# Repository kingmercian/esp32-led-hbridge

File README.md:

# ESP32 LED Controller

Schematic and PCB design for an ESP32, specifically a Wemos Lolin D2 mini shield to control low power (~200mA) monochromatic fairy lights. These monochromatic fairy lights function as bidirectional LEDs, where alternating the polarity on the two wires changes which half of the LEDs illuminate.

## Why?

My wife frequently purchases cheap battery/USB monochrome string lights at stores locally or online retailers such as Aliexpress. I wanted to be able to take advantage of these lights to automate them in my home automation system, namely a set we have covering our curtains that I would like to toggle based on sunset. https://www.aliexpress.com/item/1005007634861597.html

I was looking for a device to satisfy the following requirements:
* The device should be able to control at least one set of string lights.
* The device should be able to control the brightness of the lights.
* The device should be able to control them via  [Home Assistant](https://home-assistant.io/).

## Software
ESPHome configuration:
https://github.com/kingmercian/esphome/blob/4c16731de8fa22333e613f6e8b42984a3e44136c/curtain-leds.yaml

## Schematic

## PCB

## Render

## Parts List
| Part | Type | Footprint | Designator  | Quantity
|--|--|--|--|--|
| ESP32 S2 Mini | Microcontroller | N/A | N/A | 1 |
| 1K | Resistor| 0805 | R1, R2, R3, R4 | 4 |
| MMBT2907 | Transistor | SOT-23 | Q1, Q3 | 2 |
| MMBT2222 | Transistor | SOT-23 | Q2, Q4 | 2 |

## Issues
None for my usage but if I build these in future I would make some changes:
* add a diode between the transistor and LED output
* add terminal blocks to attach LEDs
* add button to toggle through LED patterns (control through software)
* add switch to disable LED output

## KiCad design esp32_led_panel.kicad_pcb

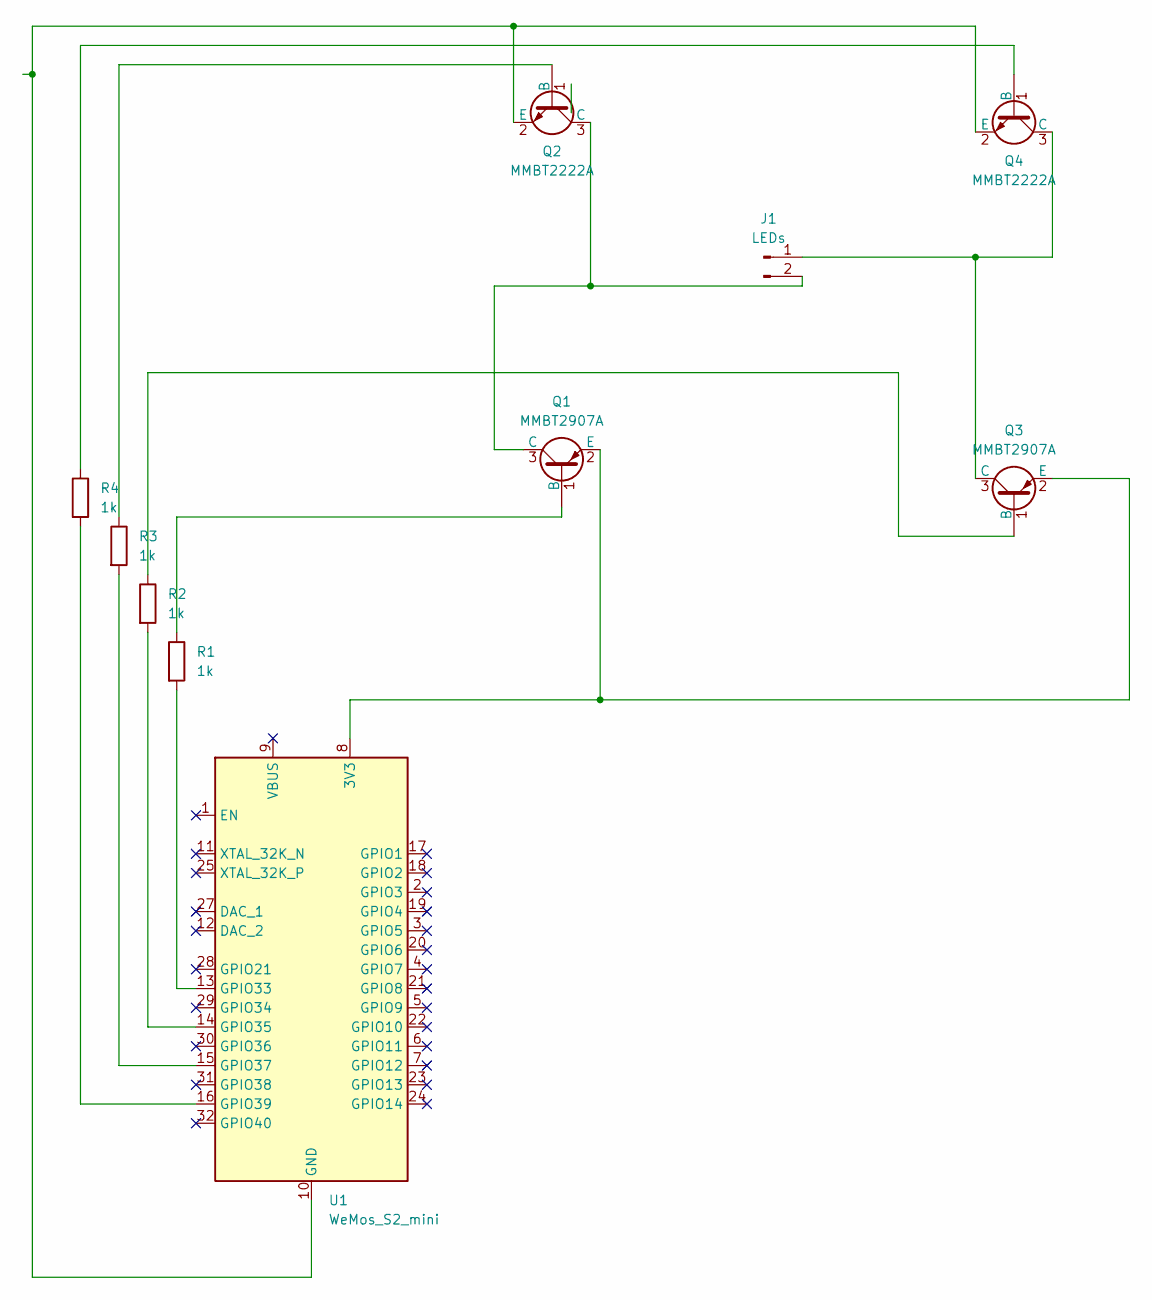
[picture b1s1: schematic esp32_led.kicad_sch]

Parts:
J1: LEDs; PinSocket_2x01_P2.54mm_Vertical
Q1, Q3: MMBT2907A; SOT-23
Q2, Q4: MMBT2222A; SOT-23
R1, R2, R3, R4: 1k; R_0805_2012Metric_Pad1.20x1.40mm_HandSolder
U1: WeMos_S2_mini; esp32_led

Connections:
unnamed: J1.1, Q3.3 (C), Q4.3 (C)
unnamed: J1.2, Q1.3 (C), Q2.3 (C)
unnamed: Q1.1 (B), R1.1
unnamed: Q1.2 (E), Q3.2 (E), U1.8 (3V3)
unnamed: Q2.1 (B), R3.1
unnamed: Q2.2 (E), Q4.2 (E), U1.10 (GND), U1.26 (GND)
unnamed: Q3.1 (B), R2.1
unnamed: Q4.1 (B), R4.1
unnamed: R1.2, U1.13 (GPIO33)
unnamed: R2.2, U1.14 (GPIO35)
unnamed: R3.2, U1.15 (GPIO37)
unnamed: R4.2, U1.16 (GPIO39)

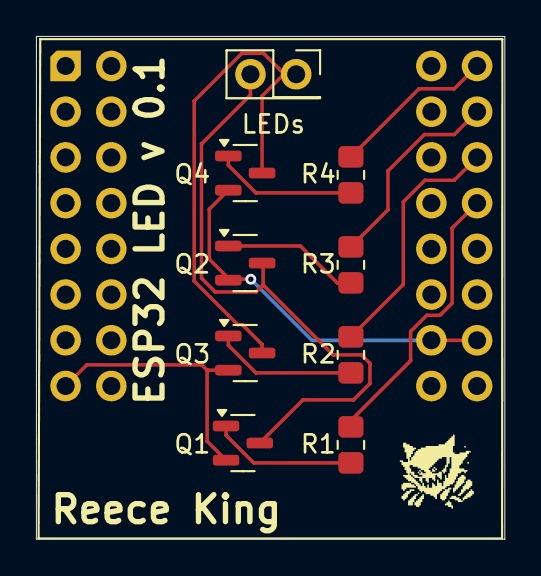
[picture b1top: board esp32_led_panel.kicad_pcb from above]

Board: 2 copper layers, 26.0 x 27.9 mm, 11 parts (0 on the bottom side), 12 nets.

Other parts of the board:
 : haunter
